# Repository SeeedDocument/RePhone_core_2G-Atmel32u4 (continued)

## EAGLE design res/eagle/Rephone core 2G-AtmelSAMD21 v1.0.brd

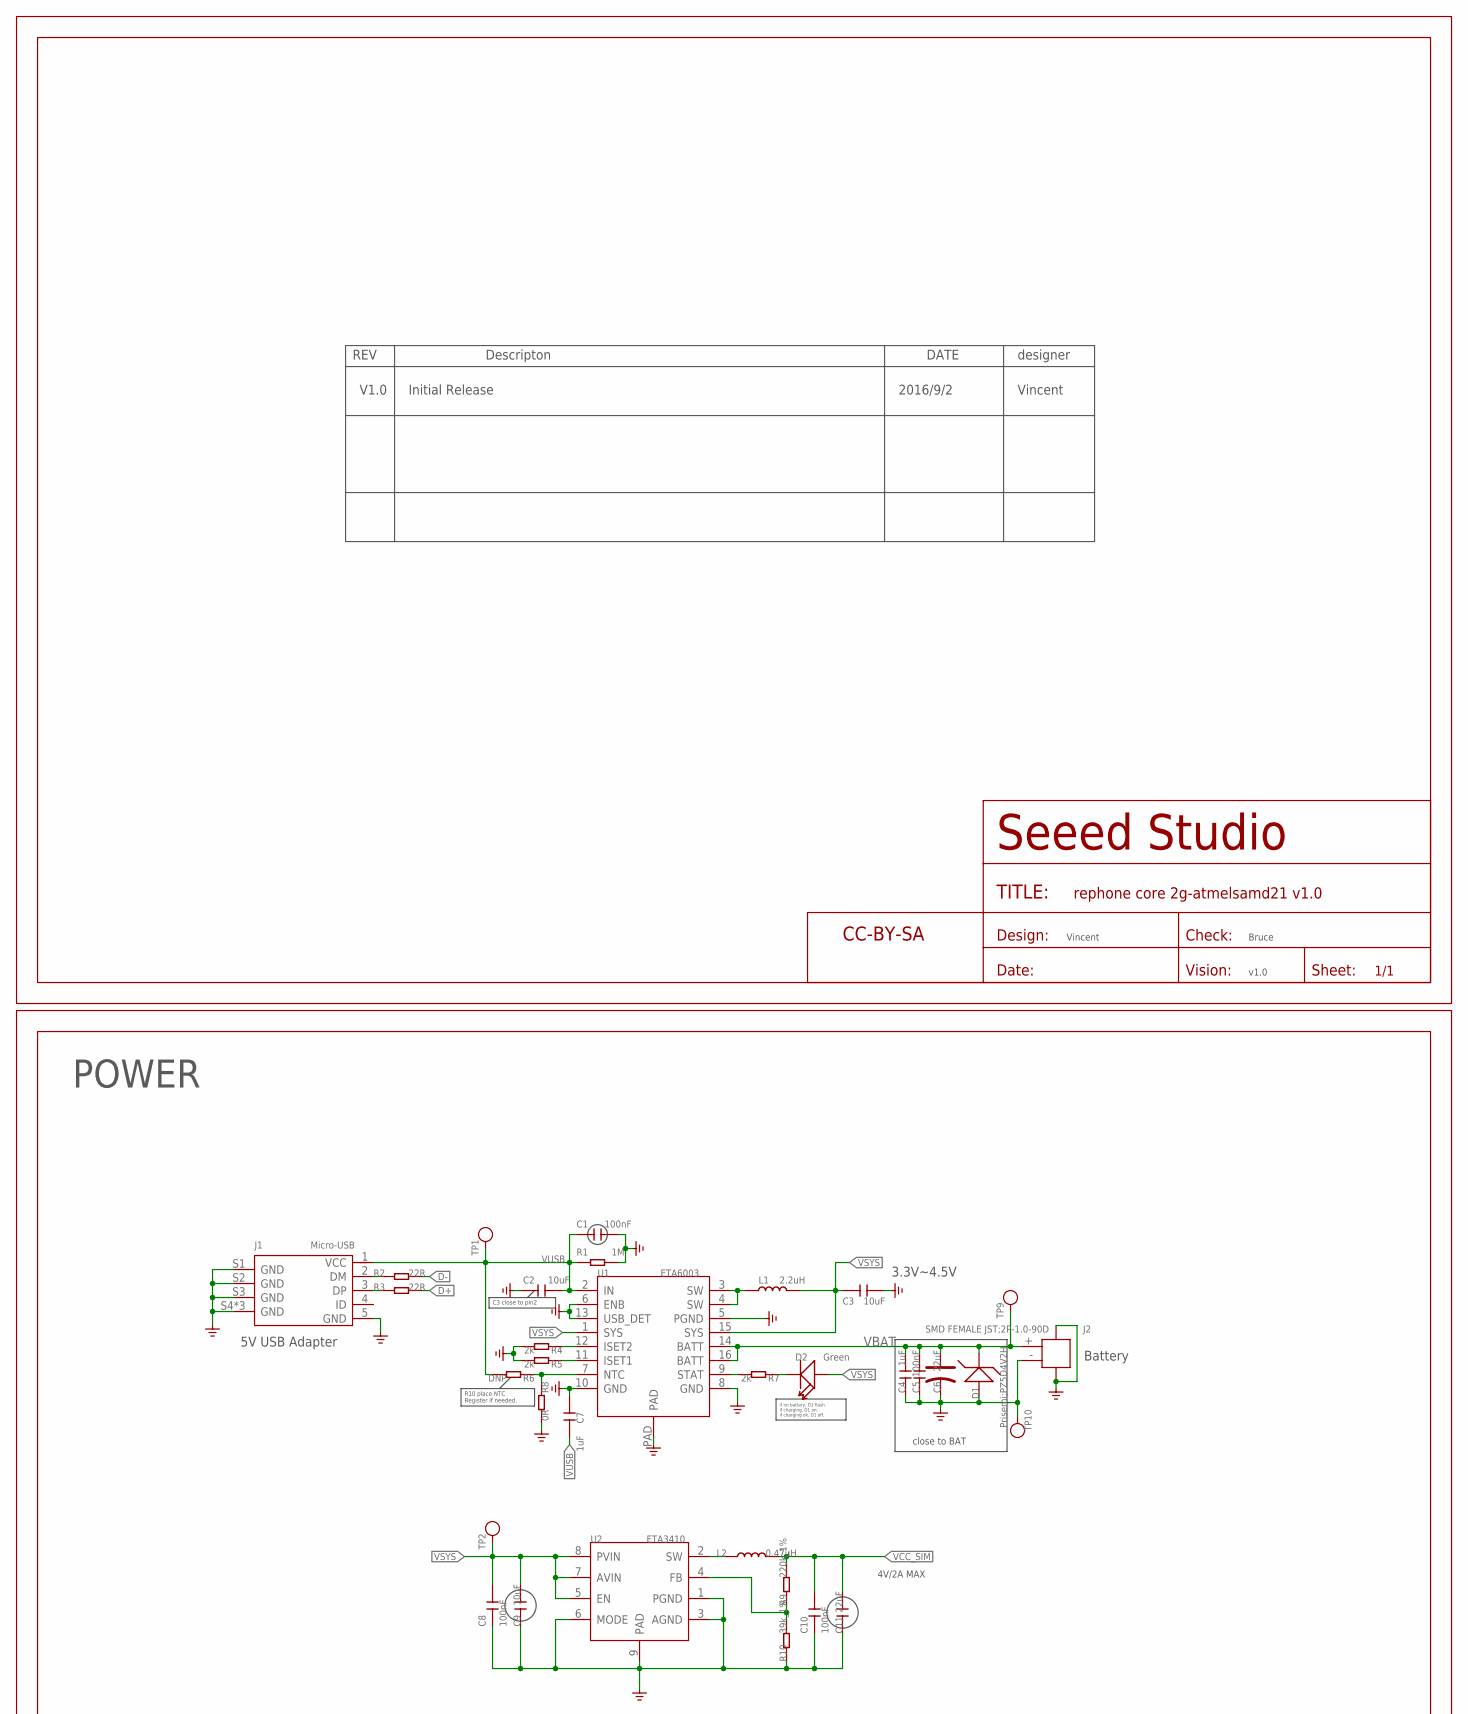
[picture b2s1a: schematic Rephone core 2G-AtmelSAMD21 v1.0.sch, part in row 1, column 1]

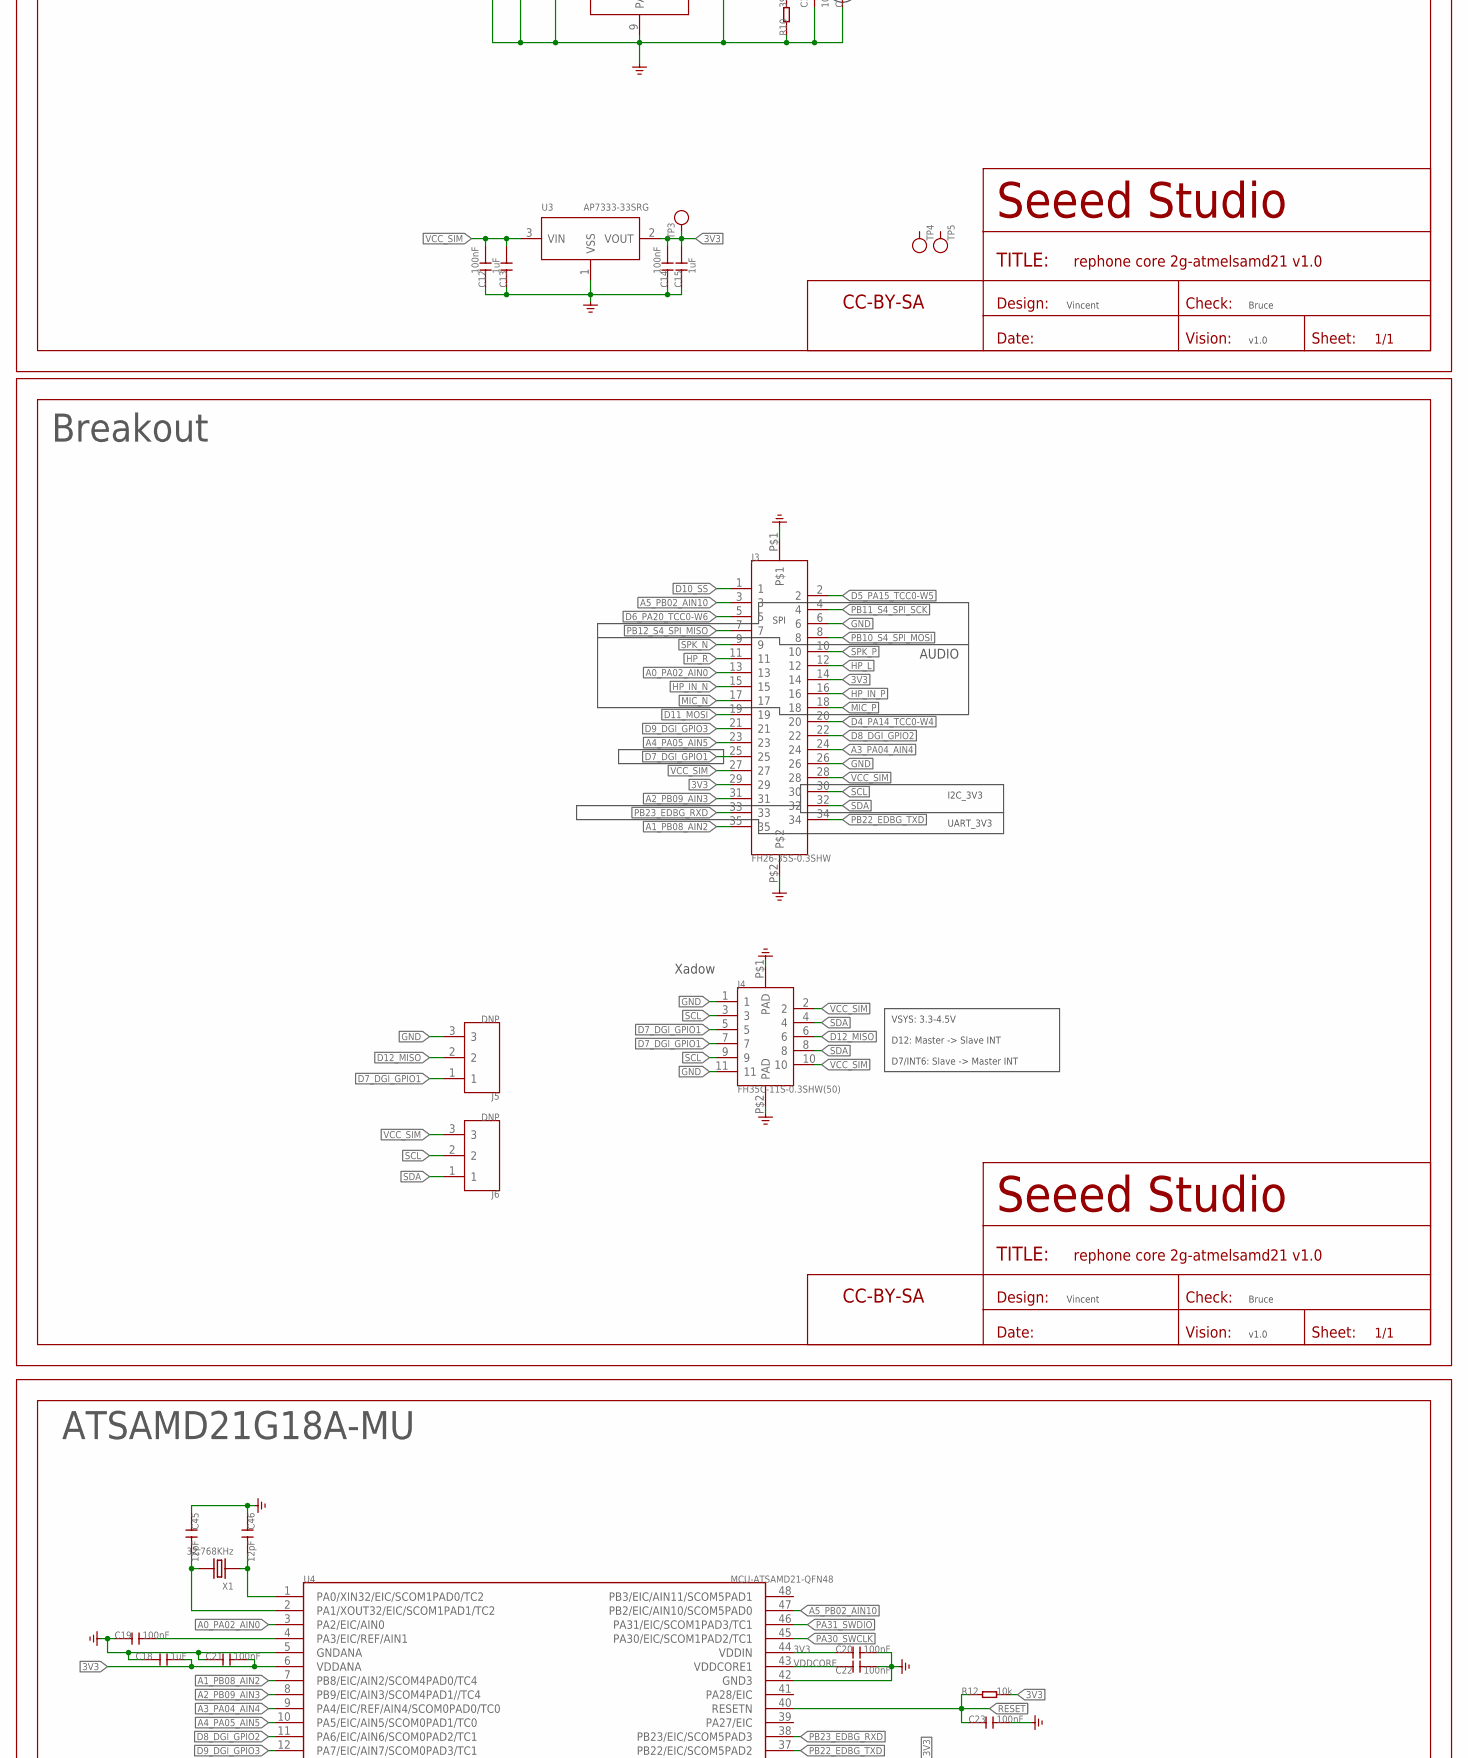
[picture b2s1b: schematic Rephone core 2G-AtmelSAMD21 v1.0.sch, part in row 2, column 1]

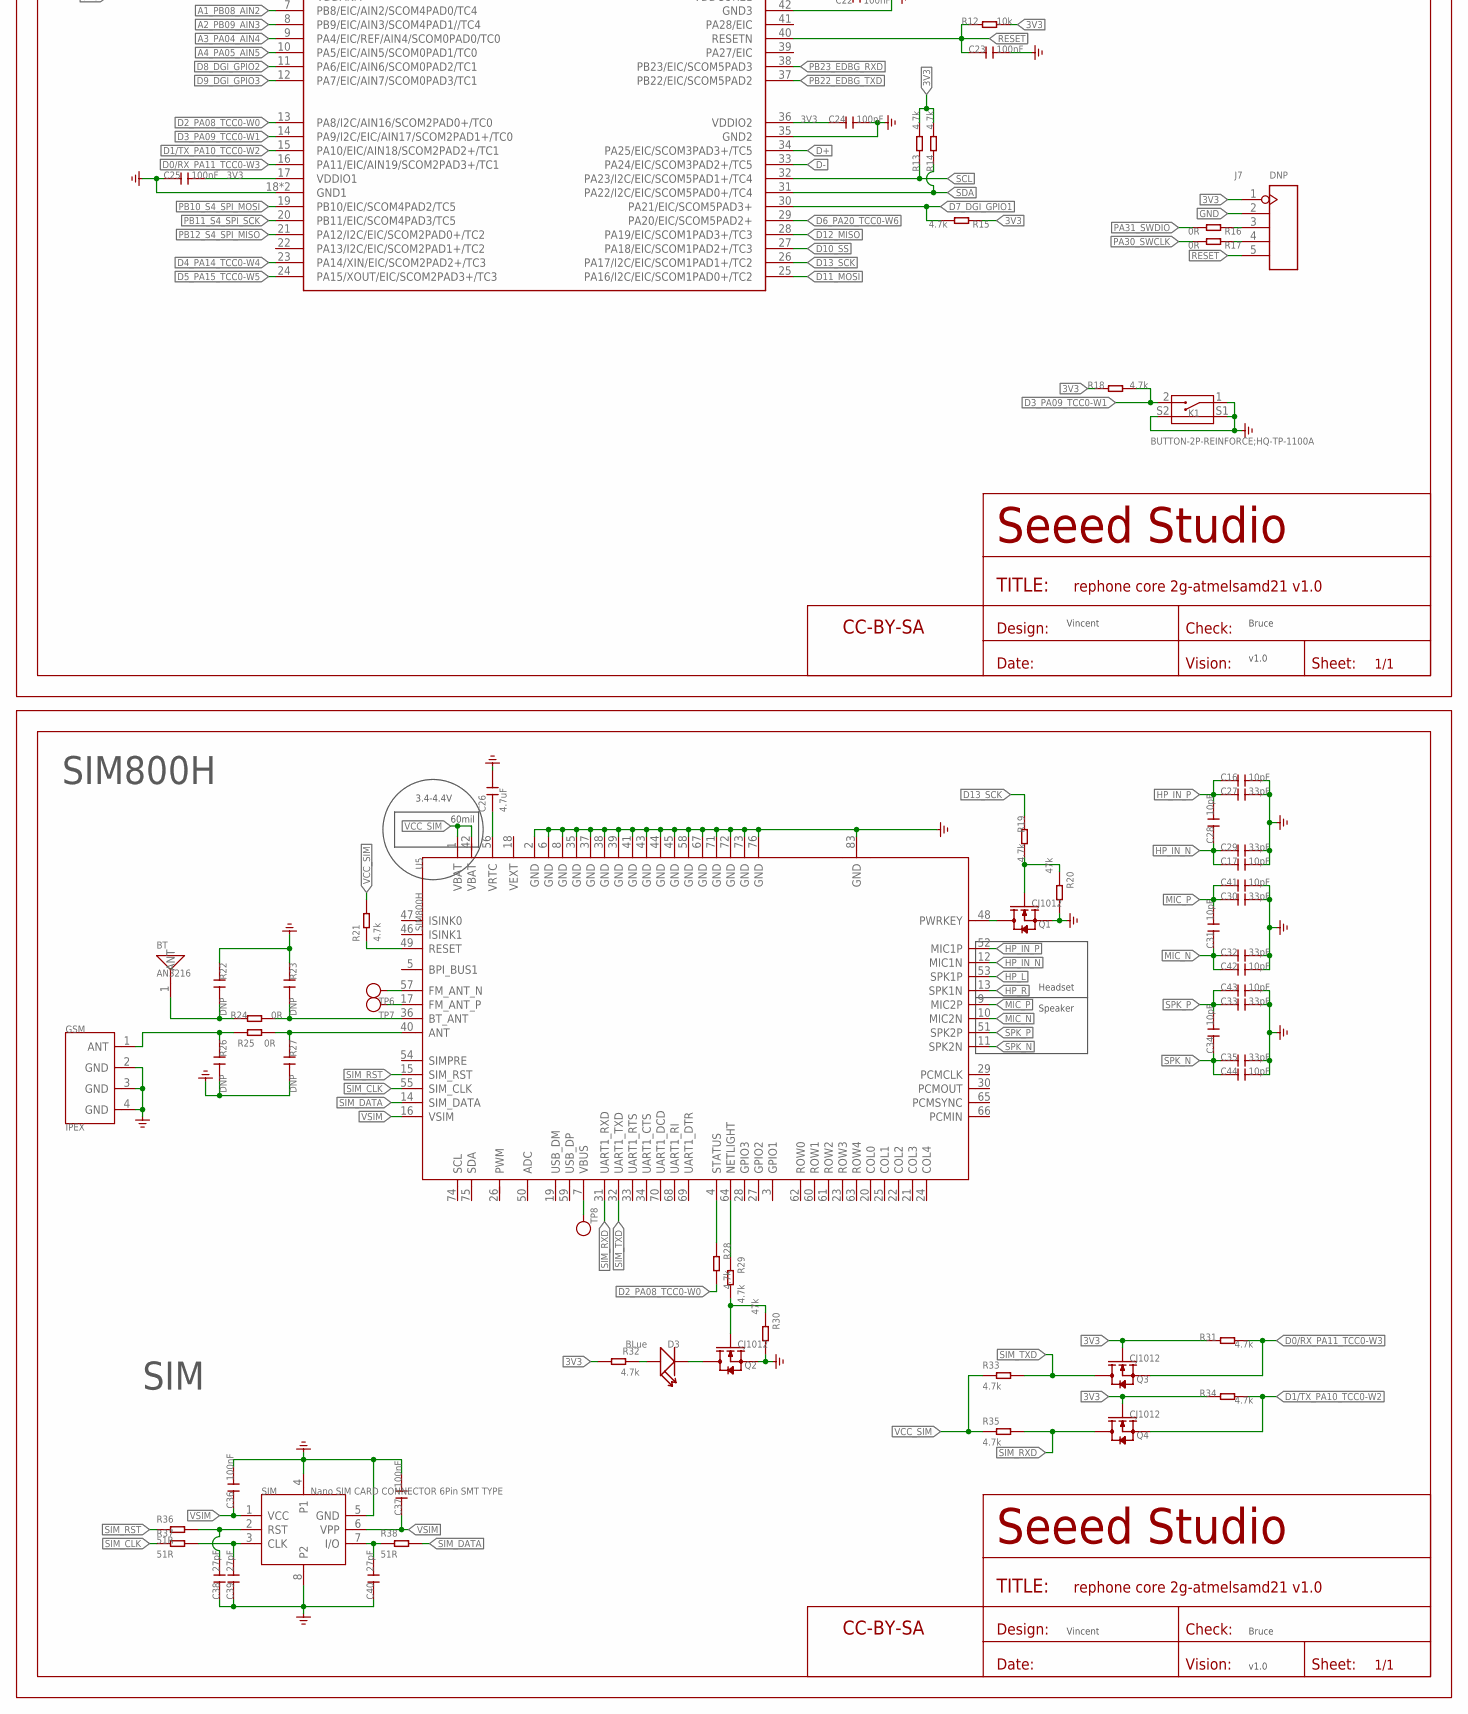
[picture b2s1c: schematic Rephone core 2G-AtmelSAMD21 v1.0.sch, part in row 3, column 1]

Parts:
BT: AN3216; ANT-SMD2P-3.2X1.6X1.04MM
C1, C5, C8, C10, C12, C14, C19, C20, C21, C22, C23, C24, C25, C36, C37: 100nF; C0201
C2, C3, C9: 10uF; C0603
C4, C7, C13, C15, C18: 1uF; C0402
C6: 22uF; AVX-A
C11: 22uF; C0603
C16, C17, C28, C31, C34, C41, C42, C43, C44: 10pF; C0201
C26: 4.7uF; C0603
C27, C29, C30, C32, C33, C35: 33pF; C0201
C38, C39, C40: 27pF; C0201
C45, C46: 12pF; C0201
D1: Prisemi;PZ5D4V2H; SOD-523
D2: Green; LED-0402
D3: BLue; LED-0402
FR1, FR2, FR3, FR4, FR5: SEEEDSTUDIO-OPEN-SCH-FRAME; SEEEDSTUDIO-PCB-FRAME
GSM: IPEX; ANT-IPEX4-1.7X1.7MM
J1: Micro-USB; MICRO-USB5+4P-SMD-0.65-B
J2: SMD FEMALE JST;2P-1.0-90D; HW2-SMD-1.0-90D
J3: FH26-35S-0.3SHW; FPC35-SMD-0.3(FH26W)
J4: FH35C-11S-0.3SHW(50); FPC11-SMD-0.3(FH35C)
J5, J6: DNP; 3P-DIP-2
J7: DNP; H5-SMD-2.0-TEST
K1: BUTTON-2P-REINFORCE;HQ-TP-1100A; SW4-SMD-4.5X3.8X1.8MM-90D
L1: 2.2uH; L0805
L2: 0.47uH; L201610
Q1, Q2, Q3, Q4: CJ1012; SOT-523
R1: 1M; R0201
R2, R3: 22R; R0201
R4, R5, R7: 2k; R0201
R6: DNP; R0201
R8, R16, R17, R24, R25: 0R; R0201
R9: 220k_1%; R0201
R10: 39k_1%; R0201
R12: 10k; R0201
R13, R14, R15, R18, R19, R21, R28, R29, R31, R32, R33, R34, R35: 4.7k; R0201
R20, R30: 47k; R0201
R22, R23, R26, R27: DNP; C0201
R36, R37, R38: 51R; R0201
SIM: Nano SIM CARD CONNECTOR 6Pin SMT TYPE; NANO-SIM6+2P-SMD-12.3X10X1.5MM
TP1, TP2, TP3, TP4, TP5, TP8, TP9, TP10: TEST-POINT-23; TP-D23MIL
TP6, TP7: TEST-POINT'4545'; TP-D45MIL
U1: ETA6003; QFN16GA-0.5-3X3MM
U2: ETA3410; DFN8G-0.5-2X2MM
U3: AP7333-33SRG; SOT-23
U4: MCU-ATSAMD21-QFN48; QFN48-7X7
U5: SIM800H; GPRS88-SMD-1.4-17.8X45.8X2.4MM
X1: 32.768KHz; X2-SMD-L2.0X1.2X0.55MM

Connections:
3V3: C14.2, C15.2, C18.2, C20.1, C21.2, C24.1, C25.2, J3.14, J3.29, J7.1, Q3.1 (G), Q4.1 (G), R12.1, R13.2, R14.2, R15.1, R18.1, R31.1, R32.2, R34.1, TP3.T, U3.2 (VOUT), U4.6 (VDDANA), U4.17 (VDDIO1), U4.36 (VDDIO2), U4.44 (VDDIN)
!RESET: C23.1, J7.5, R12.2, U4.40 (RESETN)
A0_PA02_AIN0: J3.13, U4.3 (PA2/EIC/AIN0)
A1_PB08_AIN2: J3.35, U4.7 (PB8/EIC/AIN2/SCOM4PAD0/TC4)
A2_PB09_AIN3: J3.31, U4.8 (PB9/EIC/AIN3/SCOM4PAD1//TC4)
A3_PA04_AIN4: J3.24, U4.9 (PA4/EIC/REF/AIN4/SCOM0PAD0/TC0)
A4_PA05_AIN5: J3.23, U4.10 (PA5/EIC/AIN5/SCOM0PAD1/TC0)
A5_PB02_AIN10: J3.3, U4.47 (PB2/EIC/AIN10/SCOM5PAD0)
D0/RX_PA11_TCC0-W3: Q3.2 (S), R31.2, U4.16 (PA11/EIC/AIN19/SCOM2PAD3+/TC1)
D1/TX_PA10_TCC0-W2: Q4.2 (S), R34.2, U4.15 (PA10/EIC/AIN18/SCOM2PAD2+/TC1)
D2_PA08_TCC0-W0: R28.2, U4.13 (PA8/I2C/AIN16/SCOM2PAD0+/TC0)
D3_PA09_TCC0-W1: K1.2, R18.2, U4.14 (PA9/I2C/EIC/AIN17/SCOM2PAD1+/TC0)
D4_PA14_TCC0-W4: J3.20, U4.23 (PA14/XIN/EIC/SCOM2PAD2+/TC3)
D5_PA15_TCC0-W5: J3.2, U4.24 (PA15/XOUT/EIC/SCOM2PAD3+/TC3)
D6_PA20_TCC0-W6: J3.5, U4.29 (PA20/EIC/SCOM5PAD2+)
D7_DGI_GPIO1: J3.25, J4.5, J4.7, J5.1, R15.2, U4.30 (PA21/EIC/SCOM5PAD3+)
D8_DGI_GPIO2: J3.22, U4.11 (PA6/EIC/AIN6/SCOM0PAD2/TC1)
D9_DGI_GPIO3: J3.21, U4.12 (PA7/EIC/AIN7/SCOM0PAD3/TC1)
D10_SS: J3.1, U4.27 (PA18/EIC/SCOM1PAD2+/TC3)
D11_MOSI: J3.19, U4.25 (PA16/I2C/EIC/SCOM1PAD0+/TC2)
D12_MISO: J4.6, J5.2, U4.28 (PA19/EIC/SCOM1PAD3+/TC3)
D13_SCK: R19.1, U4.26 (PA17/I2C/EIC/SCOM1PAD1+/TC2)
D+: R3.2, U4.34 (PA25/EIC/SCOM3PAD3+/TC5)
D-: R2.2, U4.33 (PA24/EIC/SCOM3PAD2+/TC5)
GND: C1.2, C2.2, C3.2, C4.2, C5.2, C6.-, C7.2, C8.1, C9.1, C10.1, C11.1, C12.1, C13.1, C14.1, C15.1, C16.2, C17.2, C18.1, C19.1, C20.2, C21.1, C22.2, C23.2, C24.2, C25.1, C26.2, C27.2, C29.2, C30.2, C32.2, C33.2, C35.2, C36.2, C37.2, C38.1, C39.1, C40.1, C41.2, C42.2, C43.2, C44.2, C45.1, C46.1, D1.+, GSM.2 (GND), GSM.3 (GND), GSM.4 (GND), J1.5 (GND), J1.S1 (GND), J1.S2 (GND), J1.S3 (GND), J1.S4 (GND), J1.S5 (GND), J1.S6 (GND), J2.3, J2.4, J2.- (2), J3.6, J3.26, J3.P$1, J3.P$2, J4.1, J4.11, J4.P$1 (PAD), J4.P$2 (PAD), J5.3, J7.2, K1.1, K1.S1, K1.S2, Q1.2 (S), Q2.2 (S), R1.2, R4.2, R5.2, R8.2, R10.1, R20.2, R22.1, R23.1, R26.2, R27.2, R30.2, SIM.4 (P1), SIM.5 (GND), SIM.8 (P2), TP10.T, U1.5 (PGND), U1.6 (ENB), U1.8 (GND), U1.10 (GND), U1.13 (USB_DET), U1.PAD, U2.1 (PGND), U2.3 (AGND), U2.6 (MODE), U2.9 (PAD), U3.1 (VSS), U4.5 (GNDANA), U4.18 (GND1), U4.35 (GND2), U4.42 (GND3), U4.PAD (GND1), U5.2 (GND), U5.6 (GND), U5.8 (GND), U5.35 (GND), U5.37 (GND), U5.38 (GND), U5.39 (GND), U5.41 (GND), U5.43 (GND), U5.44 (GND), U5.45 (GND), U5.58 (GND), U5.67 (GND), U5.71 (GND), U5.72 (GND), U5.73 (GND), U5.76 (GND), U5.83 (GND)
HP_IN_N: C17.1, C28.1, C29.1, J3.15, U5.12 (MIC1N)
HP_IN_P: C16.1, C27.1, C28.2, J3.16, U5.52 (MIC1P)
HP_L: J3.12, U5.53 (SPK1P)
HP_R: J3.11, U5.13 (SPK1N)
MIC_N: C31.1, C32.1, C42.1, J3.17, U5.10 (MIC2N)
MIC_P: C30.1, C31.2, C41.1, J3.18, U5.9 (MIC2P)
unnamed: L2.1, U2.2 (SW)
unnamed: Q1.3 (D), U5.48 (PWRKEY)
unnamed: R9.1, R10.2, U2.4 (FB)
unnamed: TP8.T, U5.7 (VBUS)
unnamed: C26.1, U5.56 (VRTC)
unnamed: C19.2, U4.4 (PA3/EIC/REF/AIN1)
unnamed: TP6.T, U5.57 (FM_ANT_N)
unnamed: TP7.T, U5.17 (FM_ANT_P)
unnamed: C39.2, R37.2, SIM.3 (CLK)
unnamed: C38.2, R36.2, SIM.2 (RST)
unnamed: Q2.1 (G), R29.2, R30.1
unnamed: R4.1, U1.12 (ISET2)
unnamed: D3.+, R32.1
unnamed: D3.-, Q2.3 (D)
unnamed: R5.1, U1.11 (ISET1)
unnamed: L1.1, U1.3 (SW), U1.4 (SW)
unnamed: R7.2, U1.9 (STAT)
unnamed: D2.-, R7.1
unnamed: R6.1, R8.1, U1.7 (NTC)
unnamed: R29.1, U5.64 (NETLIGHT)
unnamed: R21.1, U5.49 (RESET)
unnamed: Q1.1 (G), R19.2, R20.1
unnamed: J1.2 (DM), R2.1
unnamed: J1.3 (DP), R3.1
unnamed: C46.2, U4.1 (PA0/XIN32/EIC/SCOM1PAD0/TC2), X1.1
unnamed: R28.1, U5.4 (STATUS)
unnamed: BT.1, R22.2, R24.2
unnamed: GSM.1 (ANT), R25.2, R26.1
unnamed: R25.1, R27.1, U5.40 (ANT)
unnamed: R23.2, R24.1, U5.36 (BT_ANT)
unnamed: C40.2, R38.1, SIM.7 (I/O)
unnamed: J7.3, R16.1
unnamed: J7.4, R17.1
unnamed: C45.2, U4.2 (PA1/XOUT32/EIC/SCOM1PAD1/TC2), X1.2
PA30_SWCLK: R17.2, U4.45 (PA30/EIC/SCOM1PAD2/TC1)
PA31_SWDIO: R16.2, U4.46 (PA31/EIC/SCOM1PAD3/TC1)
PB10_S4_SPI_MOSI: J3.8, U4.19 (PB10/EIC/SCOM4PAD2/TC5)
PB11_S4_SPI_SCK: J3.4, U4.20 (PB11/EIC/SCOM4PAD3/TC5)
PB12_S4_SPI_MISO: J3.7, U4.21 (PA12/I2C/EIC/SCOM2PAD0+/TC2)
PB22_EDBG_TXD: J3.34, U4.37 (PB22/EIC/SCOM5PAD2)
PB23_EDBG_RXD: J3.33, U4.38 (PB23/EIC/SCOM5PAD3)
SCL: J3.30, J4.3, J4.9, J6.2, R13.1, U4.32 (PA23/I2C/EIC/SCOM5PAD1+/TC4)
SDA: J3.32, J4.4, J4.8, J6.1, R14.1, U4.31 (PA22/I2C/EIC/SCOM5PAD0+/TC4)
SIM_CLK: R37.1, U5.55 (SIM_CLK)
SIM_DATA: R38.2, U5.14 (SIM_DATA)
SIM_RST: R36.1, U5.15 (SIM_RST)
SIM_RXD: Q4.3 (D), R35.2, U5.31 (UART1_RXD)
SIM_TXD: Q3.3 (D), R33.2, U5.32 (UART1_TXD)
SPK_N: C34.1, C35.1, C44.1, J3.9, U5.11 (SPK2N)
SPK_P: C33.1, C34.2, C43.1, J3.10, U5.51 (SPK2P)
VBAT: C4.1, C5.1, C6.+, D1.-, J2.+ (1), TP9.T, U1.14 (BATT), U1.16 (BATT)
VCC_SIM: C10.2, C11.2, C12.2, C13.2, J3.27, J3.28, J4.2, J4.10, J6.3, L2.2, R9.2, R21.2, R33.1, R35.1, U3.3 (VIN), U5.1 (VBAT), U5.42 (VBAT)
VDDCORE: C22.1, U4.43 (VDDCORE1)
VSIM: C36.1, C37.1, SIM.1 (VCC), SIM.6 (VPP), U5.16 (VSIM)
VSYS: C3.1, C8.2, C9.2, D2.+, L1.2, TP2.T, U1.1 (SYS), U1.15 (SYS), U2.5 (EN), U2.7 (AVIN), U2.8 (PVIN)
VUSB: C1.1, C2.1, C7.1, J1.1 (VCC), R1.1, R6.2, TP1.T, U1.2 (IN)

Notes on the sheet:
Breakout
Xadow
POWER
SIM
AUDIO
I2C_3V3
SPI
Vincent
Bruce
v1.0
REV
Descripton
DATE
designer
R10 place NTC Register if needed.
C3 close to pin2
if no battery, D1 flash. if charging, D1 on. if charging ok, D1 off.
Battery
5V USB Adapter
3.3V~4.5V
close to BAT
ATSAMD21G18A-MU
60mil
SIM800H
D7/INT6: Slave -> Master INT
D12: Master -> Slave INT
VSYS: 3.3-4.5V
3.4-4.4V
4V/2A MAX
Speaker
Headset
UART_3V3
V1.0
Initial Release
2016/9/2

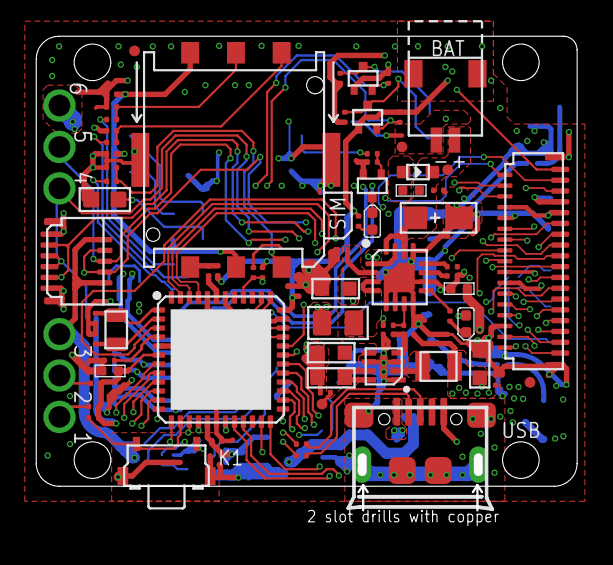
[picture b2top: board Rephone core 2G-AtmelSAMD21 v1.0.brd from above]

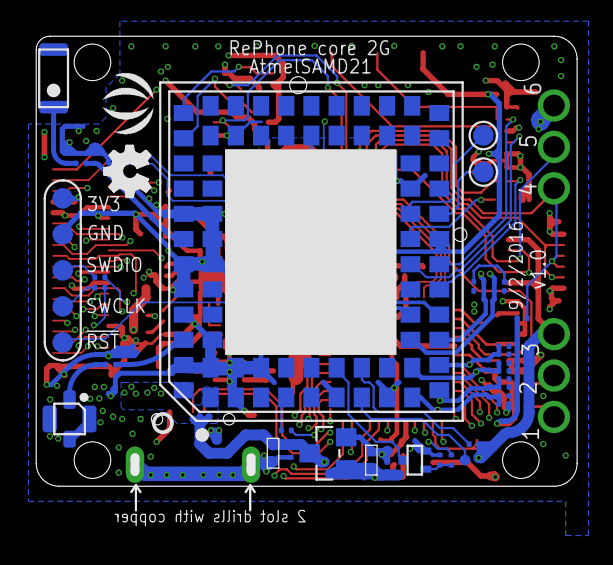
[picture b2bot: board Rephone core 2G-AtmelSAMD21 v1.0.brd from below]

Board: 4 copper layers, 30.0 x 26.3 mm, 126 parts (45 on the bottom side), 87 nets.

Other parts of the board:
U$2: SEEED-SILK-160*153MIL
U$14: OSHW_FILLX100_NOTEXT

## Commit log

2016-12-01 add resources
2016-12-27 add cover image
2016-12-27 update hw
2016-12-27 update images
